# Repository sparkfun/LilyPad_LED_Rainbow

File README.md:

LilyPad LED Rainbow Board
========================

[*LilyPad LED Rainbow Board(DEV-13903)*](https://www.sparkfun.com/products/13903)

The LilyPad LED Rainbow Board is panel containing 5 strips of 7 LilyPad LED boards, one in each of 7 colors--red, green, blue, pink, purple, yellow, and white.

Features:

* 7 LED colors
* text on board to indicate color

Repository Contents
-------------------
* **/Hardware** - PCB Design files 
* **/Production** - Panel files and any pogo bed design files

Documentation
-------------
* **[SparkFun Fritzing repo](https://github.com/sparkfun/Fritzing_Parts)** - Fritzing diagrams for SparkFun products.
* **[SparkFun 3D Model repo](https://github.com/sparkfun/3D_Models)** - 3D models of SparkFun products.
* **[Hookup Guide](https://learn.sparkfun.com/tutorials/ldk-experiment-1-lighting-up-a-basic-circuit)** - Basic hookup guide for the LilyPad Rainbow LEDs.

License Information
-------------------

This product is _**open source**_!

Please review the LICENSE.md file for license information.

If you have any questions or concerns on licensing, please contact techsupport@sparkfun.com.

Distributed as-is; no warranty is given.

- Your friends at SparkFun.

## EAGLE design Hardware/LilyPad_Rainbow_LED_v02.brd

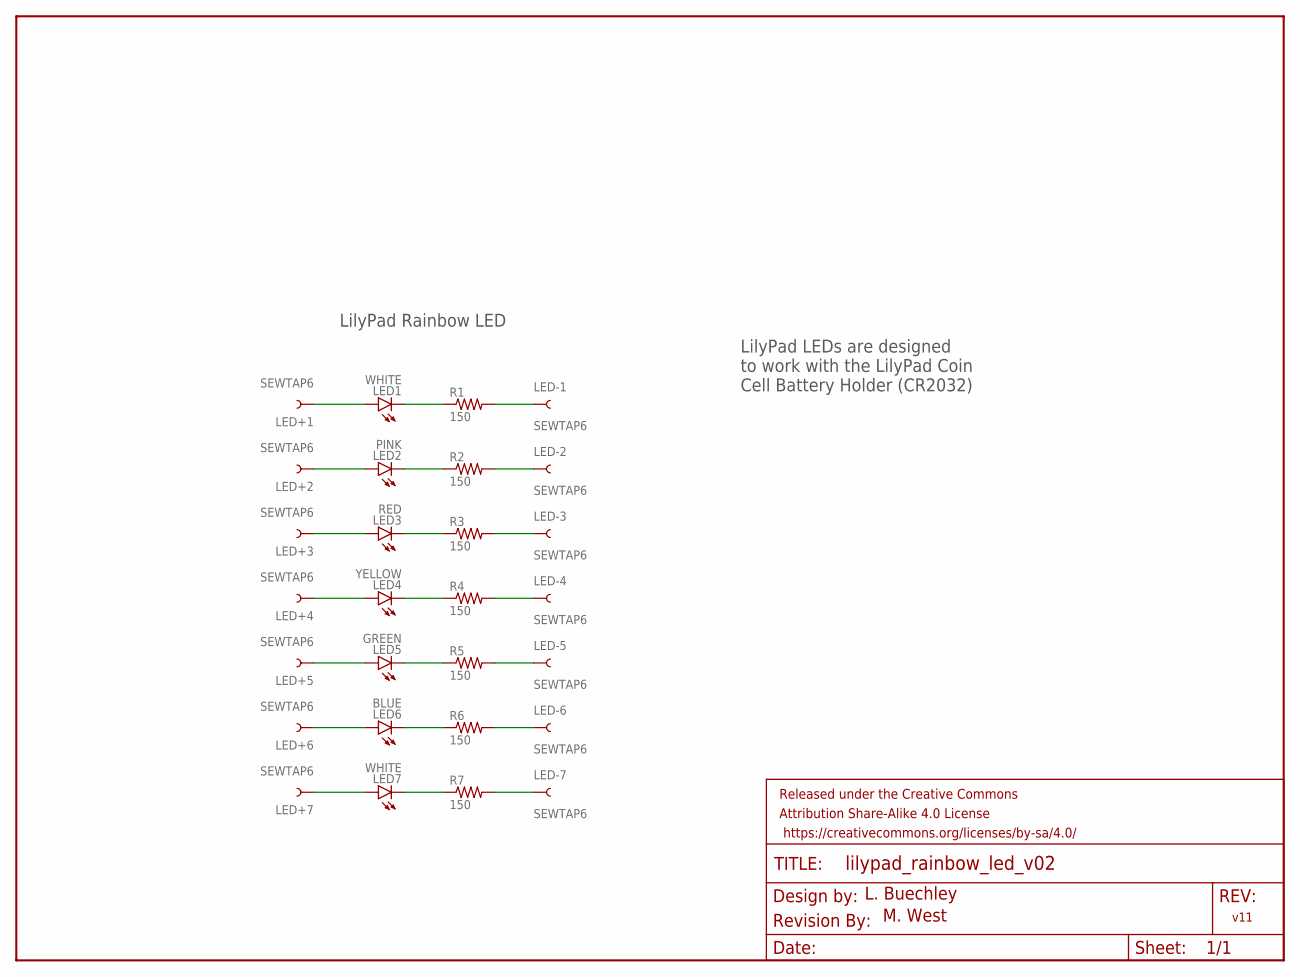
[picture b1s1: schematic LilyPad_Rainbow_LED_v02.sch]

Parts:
FRAME1: FRAME-LETTER; CREATIVE_COMMONS
LED1, LED7: WHITE; LED-1206
LED2: PINK; LED-1206
LED3: RED; LED-1206
LED4: YELLOW; LED-1206
LED5: GREEN; LED-1206
LED6: BLUE; LED-1206
LED+1, LED+2, LED+3, LED+4, LED+5, LED+6, LED+7: SEWTAP6; PETAL-SMALL-2SIDE
LED-1, LED-2, LED-3, LED-4, LED-5, LED-6, LED-7: SEWTAP6; PETAL-SMALL-2SIDE
R1, R2, R3, R4, R5, R6, R7: 150; 0603-RES
U$1: REVISION

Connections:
unnamed: LED1.A, LED+1.1
unnamed: LED1.C, R1.1
unnamed: LED-1.1, R1.2
unnamed: LED2.A, LED+2.1
unnamed: LED2.C, R2.1
unnamed: LED-2.1, R2.2
unnamed: LED3.A, LED+3.1
unnamed: LED3.C, R3.1
unnamed: LED-3.1, R3.2
unnamed: LED4.A, LED+4.1
unnamed: LED4.C, R4.1
unnamed: LED-4.1, R4.2
unnamed: LED5.A, LED+5.1
unnamed: LED5.C, R5.1
unnamed: LED-5.1, R5.2
unnamed: LED6.A, LED+6.1
unnamed: LED6.C, R6.1
unnamed: LED-6.1, R6.2
unnamed: LED7.A, LED+7.1
unnamed: LED7.C, R7.1
unnamed: LED-7.1, R7.2

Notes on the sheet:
L. Buechley
M. West
v11
LilyPad Rainbow LED
LilyPad LEDs are designed to work with the LilyPad Coin Cell Battery Holder (CR2032)

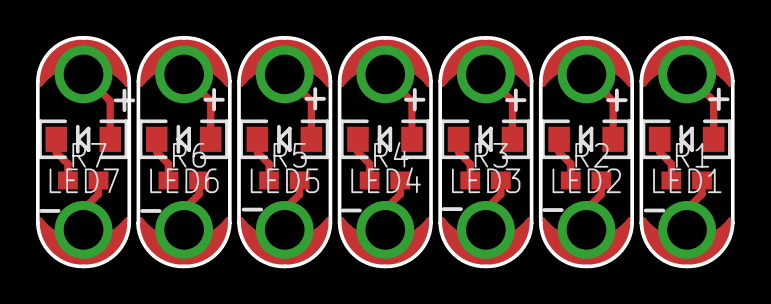
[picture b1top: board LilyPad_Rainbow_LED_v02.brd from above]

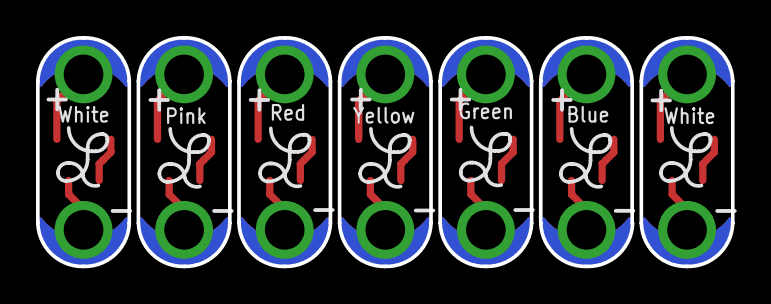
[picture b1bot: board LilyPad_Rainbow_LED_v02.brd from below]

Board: 2 copper layers, 38.6 x 12.7 mm, 37 parts (7 on the bottom side), 21 nets.

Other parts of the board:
LOGO29, LOGO30, LOGO31, LOGO32, LOGO33, LOGO34, LOGO35: LOGO-LPL; LOGO-L

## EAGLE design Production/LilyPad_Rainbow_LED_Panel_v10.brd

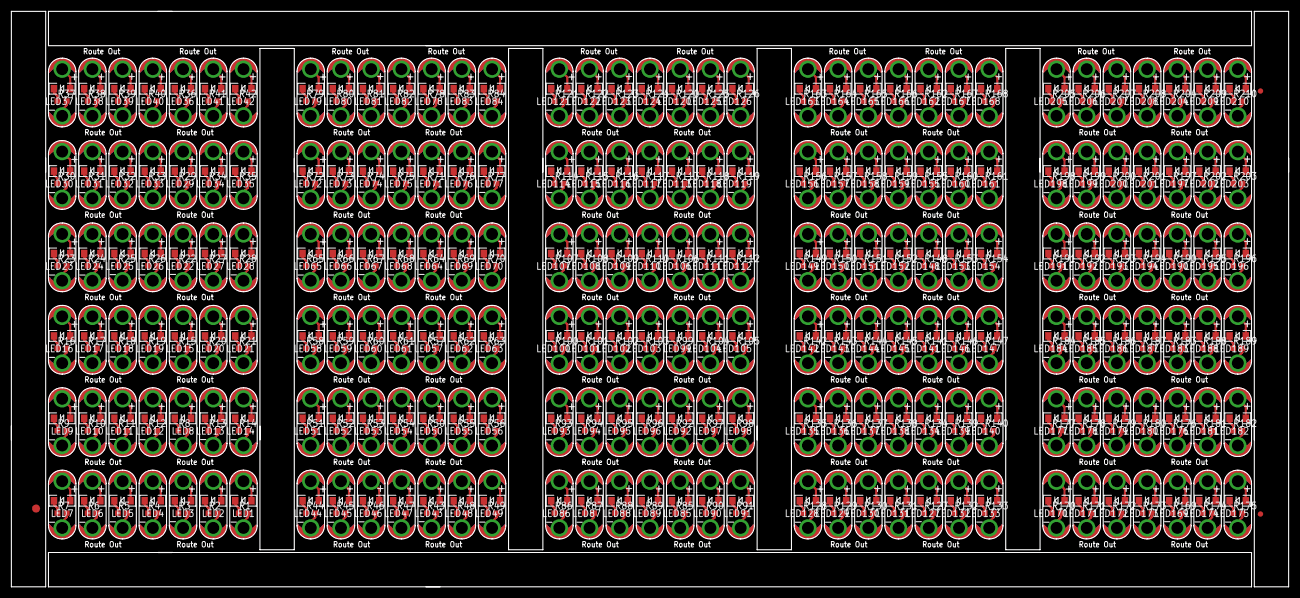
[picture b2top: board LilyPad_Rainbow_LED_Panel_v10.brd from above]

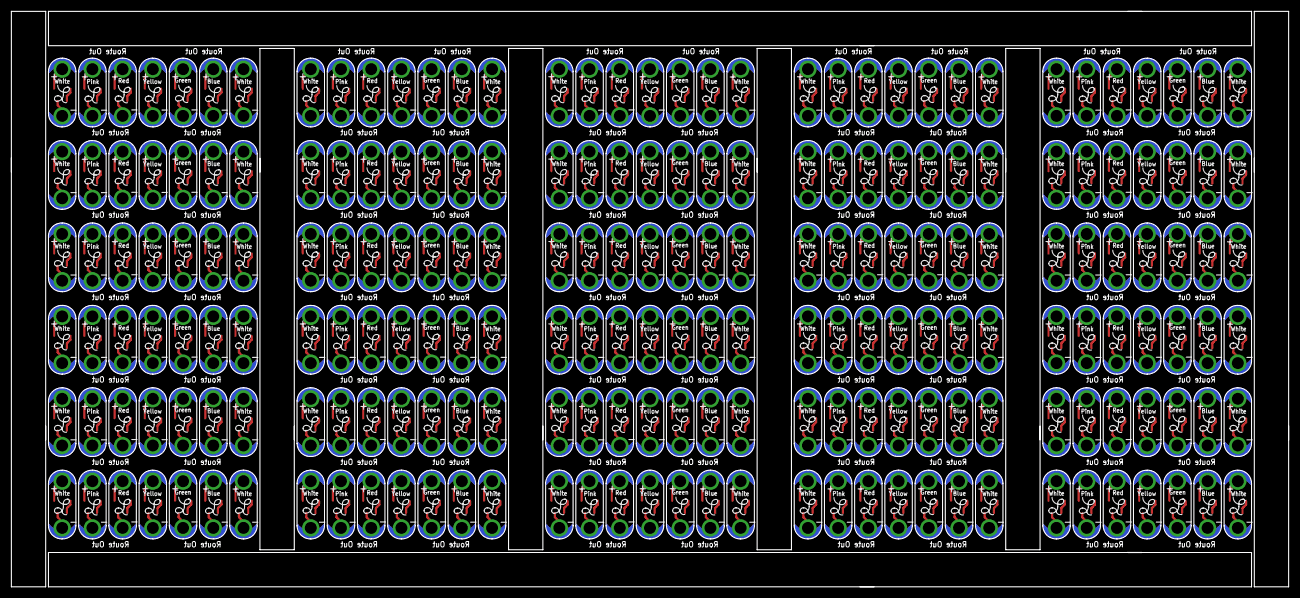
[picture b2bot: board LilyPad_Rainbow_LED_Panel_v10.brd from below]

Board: 2 copper layers, 236.2 x 106.4 mm, 1053 parts (210 on the bottom side), 630 nets.

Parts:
E$1: FIDUCIAL-1.5X3
E$13, E$14: FIDUCIAL-1X2
LED1, LED7, LED9, LED14, LED16, LED21, LED23, LED28, LED30, LED35, LED37, LED42, LED44, LED49, LED51, LED56, LED58, LED63, LED65, LED70, LED72, LED77, LED79, LED84, LED86, LED91, LED93, LED98, LED100, LED105, LED107, LED112, LED114, LED119, LED121, LED126, LED128, LED133, LED135, LED140, LED142, LED147, LED149, LED154, LED156, LED161, LED163, LED168, LED170, LED175, LED177, LED182, LED184, LED189, LED191, LED196, LED198, LED203, LED205, LED210: WHITE; LED-1206
LED2, LED13, LED20, LED27, LED34, LED41, LED48, LED55, LED62, LED69, LED76, LED83, LED90, LED97, LED104, LED111, LED118, LED125, LED132, LED139, LED146, LED153, LED160, LED167, LED174, LED181, LED188, LED195, LED202, LED209: PINK; LED-1206
LED3, LED8, LED15, LED22, LED29, LED36, LED43, LED50, LED57, LED64, LED71, LED78, LED85, LED92, LED99, LED106, LED113, LED120, LED127, LED134, LED141, LED148, LED155, LED162, LED169, LED176, LED183, LED190, LED197, LED204: RED; LED-1206
LED4, LED12, LED19, LED26, LED33, LED40, LED47, LED54, LED61, LED68, LED75, LED82, LED89, LED96, LED103, LED110, LED117, LED124, LED131, LED138, LED145, LED152, LED159, LED166, LED173, LED180, LED187, LED194, LED201, LED208: YELLOW; LED-1206
LED5, LED11, LED18, LED25, LED32, LED39, LED46, LED53, LED60, LED67, LED74, LED81, LED88, LED95, LED102, LED109, LED116, LED123, LED130, LED137, LED144, LED151, LED158, LED165, LED172, LED179, LED186, LED193, LED200, LED207: GREEN; LED-1206
LED6, LED10, LED17, LED24, LED31, LED38, LED45, LED52, LED59, LED66, LED73, LED80, LED87, LED94, LED101, LED108, LED115, LED122, LED129, LED136, LED143, LED150, LED157, LED164, LED171, LED178, LED185, LED192, LED199, LED206: BLUE; LED-1206
LED+1, LED+2, LED+3, LED+4, LED+5, LED+6, LED+7, LED+8, LED+9, LED+10, LED+11, LED+12, LED+13, LED+14, LED+15, LED+16, LED+17, LED+18, LED+19, LED+20, LED+21, LED+22, LED+23, LED+24, LED+25, LED+26, LED+27, LED+28, LED+29, LED+30, LED+31, LED+32, LED+33, LED+34, LED+35, LED+36, LED+37, LED+38, LED+39, LED+40, LED+41, LED+42, LED+43, LED+44, LED+45, LED+46, LED+47, LED+48, LED+49, LED+50, LED+51, LED+52, LED+53, LED+54, LED+55, LED+56, LED+57, LED+58, LED+59, LED+60, LED+61, LED+62, LED+63, LED+64, LED+65, LED+66, LED+67, LED+68, LED+69, LED+70, LED+71, LED+72, LED+73, LED+74, LED+75, LED+76, LED+77, LED+78, LED+79, LED+80, LED+81, LED+82, LED+83, LED+84, LED+85, LED+86, LED+87, LED+88, LED+89, LED+90, LED+91, LED+92, LED+93, LED+94, LED+95, LED+96, LED+97, LED+98, LED+99, LED+100, LED+101, LED+102, LED+103, LED+104, LED+105, LED+106, LED+107, LED+108, LED+109, LED+110, LED+111, LED+112, LED+113, LED+114, LED+115, LED+116, LED+117, LED+118, LED+119, LED+120, LED+121, LED+122, LED+123, LED+124, LED+125, LED+126, LED+127, LED+128, LED+129, LED+130, LED+131, LED+132, LED+133, LED+134, LED+135, LED+136, LED+137, LED+138, LED+139, LED+140, LED+141, LED+142, LED+143, LED+144, LED+145, LED+146, LED+147, LED+148, LED+149, LED+150, LED+151, LED+152, LED+153, LED+154, LED+155, LED+156, LED+157, LED+158, LED+159, LED+160, LED+161, LED+162, LED+163, LED+164, LED+165, LED+166, LED+167, LED+168, LED+169, LED+170, LED+171, LED+172, LED+173, LED+174, LED+175, LED+176, LED+177, LED+178, LED+179, LED+180, LED+181, LED+182, LED+183, LED+184, LED+185, LED+186, LED+187, LED+188, LED+189, LED+190, LED+191, LED+192, LED+193, LED+194, LED+195, LED+196, LED+197, LED+198, LED+199, LED+200, LED+201, LED+202, LED+203, LED+204, LED+205, LED+206, LED+207, LED+208, LED+209, LED+210: SEWTAP6; PETAL-SMALL-2SIDE
LED-1, LED-2, LED-3, LED-4, LED-5, LED-6, LED-7, LED-8, LED-9, LED-10, LED-11, LED-12, LED-13, LED-14, LED-15, LED-16, LED-17, LED-18, LED-19, LED-20, LED-21, LED-22, LED-23, LED-24, LED-25, LED-26, LED-27, LED-28, LED-29, LED-30, LED-31, LED-32, LED-33, LED-34, LED-35, LED-36, LED-37, LED-38, LED-39, LED-40, LED-41, LED-42, LED-43, LED-44, LED-45, LED-46, LED-47, LED-48, LED-49, LED-50, LED-51, LED-52, LED-53, LED-54, LED-55, LED-56, LED-57, LED-58, LED-59, LED-60, LED-61, LED-62, LED-63, LED-64, LED-65, LED-66, LED-67, LED-68, LED-69, LED-70, LED-71, LED-72, LED-73, LED-74, LED-75, LED-76, LED-77, LED-78, LED-79, LED-80, LED-81, LED-82, LED-83, LED-84, LED-85, LED-86, LED-87, LED-88, LED-89, LED-90, LED-91, LED-92, LED-93, LED-94, LED-95, LED-96, LED-97, LED-98, LED-99, LED-100, LED-101, LED-102, LED-103, LED-104, LED-105, LED-106, LED-107, LED-108, LED-109, LED-110, LED-111, LED-112, LED-113, LED-114, LED-115, LED-116, LED-117, LED-118, LED-119, LED-120, LED-121, LED-122, LED-123, LED-124, LED-125, LED-126, LED-127, LED-128, LED-129, LED-130, LED-131, LED-132, LED-133, LED-134, LED-135, LED-136, LED-137, LED-138, LED-139, LED-140, LED-141, LED-142, LED-143, LED-144, LED-145, LED-146, LED-147, LED-148, LED-149, LED-150, LED-151, LED-152, LED-153, LED-154, LED-155, LED-156, LED-157, LED-158, LED-159, LED-160, LED-161, LED-162, LED-163, LED-164, LED-165, LED-166, LED-167, LED-168, LED-169, LED-170, LED-171, LED-172, LED-173, LED-174, LED-175, LED-176, LED-177, LED-178, LED-179, LED-180, LED-181, LED-182, LED-183, LED-184, LED-185, LED-186, LED-187, LED-188, LED-189, LED-190, LED-191, LED-192, LED-193, LED-194, LED-195, LED-196, LED-197, LED-198, LED-199, LED-200, LED-201, LED-202, LED-203, LED-204, LED-205, LED-206, LED-207, LED-208, LED-209, LED-210: SEWTAP6; PETAL-SMALL-2SIDE
LOGO1, LOGO2, LOGO3, LOGO4, LOGO5, LOGO6, LOGO7, LOGO8, LOGO9, LOGO10, LOGO11, LOGO12, LOGO13, LOGO14, LOGO15, LOGO16, LOGO17, LOGO18, LOGO19, LOGO20, LOGO21, LOGO22, LOGO23, LOGO24, LOGO25, LOGO26, LOGO27, LOGO28, LOGO29, LOGO30, LOGO31, LOGO32, LOGO33, LOGO34, LOGO35, LOGO36, LOGO37, LOGO38, LOGO39, LOGO40, LOGO41, LOGO42, LOGO43, LOGO44, LOGO45, LOGO46, LOGO47, LOGO48, LOGO49, LOGO50, LOGO51, LOGO52, LOGO53, LOGO54, LOGO55, LOGO56, LOGO57, LOGO58, LOGO59, LOGO60, LOGO61, LOGO62, LOGO63, LOGO64, LOGO65, LOGO66, LOGO67, LOGO68, LOGO69, LOGO70, LOGO71, LOGO72, LOGO73, LOGO74, LOGO75, LOGO76, LOGO77, LOGO78, LOGO79, LOGO80, LOGO81, LOGO82, LOGO83, LOGO84, LOGO85, LOGO86, LOGO87, LOGO88, LOGO89, LOGO90, LOGO91, LOGO92, LOGO93, LOGO94, LOGO95, LOGO96, LOGO97, LOGO98, LOGO99, LOGO100, LOGO101, LOGO102, LOGO103, LOGO104, LOGO105, LOGO106, LOGO107, LOGO108, LOGO109, LOGO110, LOGO111, LOGO112, LOGO113, LOGO114, LOGO115, LOGO116, LOGO117, LOGO118, LOGO119, LOGO120, LOGO121, LOGO122, LOGO123, LOGO124, LOGO125, LOGO126, LOGO127, LOGO128, LOGO129, LOGO130, LOGO131, LOGO132, LOGO133, LOGO134, LOGO135, LOGO136, LOGO137, LOGO138, LOGO139, LOGO140, LOGO141, LOGO142, LOGO143, LOGO144, LOGO145, LOGO146, LOGO147, LOGO148, LOGO149, LOGO150, LOGO151, LOGO152, LOGO153, LOGO154, LOGO155, LOGO156, LOGO157, LOGO158, LOGO159, LOGO160, LOGO161, LOGO162, LOGO163, LOGO164, LOGO165, LOGO166, LOGO167, LOGO168, LOGO169, LOGO170, LOGO171, LOGO172, LOGO173, LOGO174, LOGO175, LOGO176, LOGO177, LOGO178, LOGO179, LOGO180, LOGO181, LOGO182, LOGO183, LOGO184, LOGO185, LOGO186, LOGO187, LOGO188, LOGO189, LOGO190, LOGO191, LOGO192, LOGO193, LOGO194, LOGO195, LOGO196, LOGO197, LOGO198, LOGO199, LOGO200, LOGO201, LOGO202, LOGO203, LOGO204, LOGO205, LOGO206, LOGO207, LOGO208, LOGO209, LOGO210: LOGO-LPL; LOGO-L
R1, R2, R3, R4, R5, R6, R7, R8, R9, R10, R11, R12, R13, R14, R15, R16, R17, R18, R19, R20, R21, R22, R23, R24, R25, R26, R27, R28, R29, R30, R31, R32, R33, R34, R35, R36, R37, R38, R39, R40, R41, R42, R43, R44, R45, R46, R47, R48, R49, R50, R51, R52, R53, R54, R55, R56, R57, R58, R59, R60, R61, R62, R63, R64, R65, R66, R67, R68, R69, R70, R71, R72, R73, R74, R75, R76, R77, R78, R79, R80, R81, R82, R83, R84, R85, R86, R87, R88, R89, R90, R91, R92, R93, R94, R95, R96, R97, R98, R99, R100, R101, R102, R103, R104, R105, R106, R107, R108, R109, R110, R111, R112, R113, R114, R115, R116, R117, R118, R119, R120, R121, R122, R123, R124, R125, R126, R127, R128, R129, R130, R131, R132, R133, R134, R135, R136, R137, R138, R139, R140, R141, R142, R143, R144, R145, R146, R147, R148, R149, R150, R151, R152, R153, R154, R155, R156, R157, R158, R159, R160, R161, R162, R163, R164, R165, R166, R167, R168, R169, R170, R171, R172, R173, R174, R175, R176, R177, R178, R179, R180, R181, R182, R183, R184, R185, R186, R187, R188, R189, R190, R191, R192, R193, R194, R195, R196, R197, R198, R199, R200, R201, R202, R203, R204, R205, R206, R207, R208, R209, R210: 150; 0603-RES

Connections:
unnamed: LED1.A, LED+1.1
unnamed: LED1.C, R1.1
unnamed: LED-1.1, R1.2
unnamed: LED2.A, LED+2.1
unnamed: LED2.C, R2.1
unnamed: LED-2.1, R2.2
unnamed: LED3.A, LED+3.1
unnamed: LED3.C, R3.1
unnamed: LED-3.1, R3.2
unnamed: LED4.A, LED+4.1
unnamed: LED4.C, R4.1
unnamed: LED-4.1, R4.2
unnamed: LED5.A, LED+5.1
unnamed: LED5.C, R5.1
unnamed: LED-5.1, R5.2
unnamed: LED6.A, LED+6.1
unnamed: LED6.C, R6.1
unnamed: LED-6.1, R6.2
unnamed: LED7.A, LED+7.1
unnamed: LED7.C, R7.1
unnamed: LED-7.1, R7.2
unnamed: LED8.C, R8.1
unnamed: LED8.A, LED+8.1
unnamed: LED-8.1, R8.2
unnamed: LED9.C, R9.1
unnamed: LED9.A, LED+9.1
unnamed: LED-9.1, R9.2
unnamed: LED10.C, R10.1
unnamed: LED10.A, LED+10.1
unnamed: LED-10.1, R10.2
unnamed: LED11.C, R11.1
unnamed: LED11.A, LED+11.1
unnamed: LED-11.1, R11.2
unnamed: LED12.C, R12.1
unnamed: LED12.A, LED+12.1
unnamed: LED-12.1, R12.2
unnamed: LED13.C, R13.1
unnamed: LED13.A, LED+13.1
unnamed: LED-13.1, R13.2
unnamed: LED14.C, R14.1
unnamed: LED14.A, LED+14.1
unnamed: LED-14.1, R14.2
unnamed: LED15.C, R15.1
unnamed: LED15.A, LED+15.1
unnamed: LED-15.1, R15.2
unnamed: LED16.C, R16.1
unnamed: LED16.A, LED+16.1
unnamed: LED-16.1, R16.2
unnamed: LED17.C, R17.1
unnamed: LED17.A, LED+17.1
unnamed: LED-17.1, R17.2
unnamed: LED18.C, R18.1
unnamed: LED18.A, LED+18.1
unnamed: LED-18.1, R18.2
unnamed: LED19.C, R19.1
unnamed: LED19.A, LED+19.1
unnamed: LED-19.1, R19.2
unnamed: LED20.C, R20.1
unnamed: LED20.A, LED+20.1
unnamed: LED-20.1, R20.2
unnamed: LED21.C, R21.1
unnamed: LED21.A, LED+21.1
unnamed: LED-21.1, R21.2
unnamed: LED22.C, R22.1
unnamed: LED22.A, LED+22.1
unnamed: LED-22.1, R22.2
unnamed: LED23.C, R23.1
unnamed: LED23.A, LED+23.1
unnamed: LED-23.1, R23.2
unnamed: LED24.C, R24.1
unnamed: LED24.A, LED+24.1
unnamed: LED-24.1, R24.2
unnamed: LED25.C, R25.1
unnamed: LED25.A, LED+25.1
unnamed: LED-25.1, R25.2
unnamed: LED26.C, R26.1
unnamed: LED26.A, LED+26.1
unnamed: LED-26.1, R26.2
unnamed: LED27.C, R27.1
unnamed: LED27.A, LED+27.1
unnamed: LED-27.1, R27.2
unnamed: LED28.C, R28.1
unnamed: LED28.A, LED+28.1
unnamed: LED-28.1, R28.2
unnamed: LED29.C, R29.1
unnamed: LED29.A, LED+29.1
unnamed: LED-29.1, R29.2
unnamed: LED30.C, R30.1
unnamed: LED30.A, LED+30.1
unnamed: LED-30.1, R30.2
unnamed: LED31.C, R31.1
unnamed: LED31.A, LED+31.1
unnamed: LED-31.1, R31.2
unnamed: LED32.C, R32.1
unnamed: LED32.A, LED+32.1
unnamed: LED-32.1, R32.2
unnamed: LED33.C, R33.1
unnamed: LED33.A, LED+33.1
unnamed: LED-33.1, R33.2
unnamed: LED34.C, R34.1
unnamed: LED34.A, LED+34.1
unnamed: LED-34.1, R34.2
unnamed: LED35.C, R35.1
unnamed: LED35.A, LED+35.1
unnamed: LED-35.1, R35.2
unnamed: LED36.C, R36.1
unnamed: LED36.A, LED+36.1
unnamed: LED-36.1, R36.2
unnamed: LED37.C, R37.1
unnamed: LED37.A, LED+37.1
unnamed: LED-37.1, R37.2
unnamed: LED38.C, R38.1
unnamed: LED38.A, LED+38.1
unnamed: LED-38.1, R38.2
unnamed: LED39.C, R39.1
unnamed: LED39.A, LED+39.1
unnamed: LED-39.1, R39.2
unnamed: LED40.C, R40.1
unnamed: LED40.A, LED+40.1
unnamed: LED-40.1, R40.2
unnamed: LED41.C, R41.1
unnamed: LED41.A, LED+41.1
unnamed: LED-41.1, R41.2
unnamed: LED42.C, R42.1
unnamed: LED42.A, LED+42.1
unnamed: LED-42.1, R42.2
unnamed: LED43.C, R43.1
unnamed: LED43.A, LED+43.1
unnamed: LED-43.1, R43.2
unnamed: LED44.C, R44.1
unnamed: LED44.A, LED+44.1
unnamed: LED-44.1, R44.2
unnamed: LED45.C, R45.1
unnamed: LED45.A, LED+45.1
unnamed: LED-45.1, R45.2
unnamed: LED46.C, R46.1
unnamed: LED46.A, LED+46.1
unnamed: LED-46.1, R46.2
unnamed: LED47.C, R47.1
unnamed: LED47.A, LED+47.1
unnamed: LED-47.1, R47.2
unnamed: LED48.C, R48.1
unnamed: LED48.A, LED+48.1
unnamed: LED-48.1, R48.2
unnamed: LED49.C, R49.1
unnamed: LED49.A, LED+49.1
unnamed: LED-49.1, R49.2
unnamed: LED50.C, R50.1
unnamed: LED50.A, LED+50.1
unnamed: LED-50.1, R50.2
unnamed: LED51.C, R51.1
unnamed: LED51.A, LED+51.1
unnamed: LED-51.1, R51.2
unnamed: LED52.C, R52.1
unnamed: LED52.A, LED+52.1
unnamed: LED-52.1, R52.2
unnamed: LED53.C, R53.1
unnamed: LED53.A, LED+53.1
unnamed: LED-53.1, R53.2
unnamed: LED54.C, R54.1
unnamed: LED54.A, LED+54.1
unnamed: LED-54.1, R54.2
unnamed: LED55.C, R55.1
unnamed: LED55.A, LED+55.1
unnamed: LED-55.1, R55.2
unnamed: LED56.C, R56.1
unnamed: LED56.A, LED+56.1
unnamed: LED-56.1, R56.2
unnamed: LED57.C, R57.1
unnamed: LED57.A, LED+57.1
unnamed: LED-57.1, R57.2
unnamed: LED58.C, R58.1
unnamed: LED58.A, LED+58.1
unnamed: LED-58.1, R58.2
unnamed: LED59.C, R59.1
unnamed: LED59.A, LED+59.1
unnamed: LED-59.1, R59.2
unnamed: LED60.C, R60.1
unnamed: LED60.A, LED+60.1
unnamed: LED-60.1, R60.2
unnamed: LED61.C, R61.1
unnamed: LED61.A, LED+61.1
unnamed: LED-61.1, R61.2
unnamed: LED62.C, R62.1
unnamed: LED62.A, LED+62.1
unnamed: LED-62.1, R62.2
unnamed: LED63.C, R63.1
unnamed: LED63.A, LED+63.1
unnamed: LED-63.1, R63.2
unnamed: LED64.C, R64.1
unnamed: LED64.A, LED+64.1
unnamed: LED-64.1, R64.2
unnamed: LED65.C, R65.1
unnamed: LED65.A, LED+65.1
unnamed: LED-65.1, R65.2
unnamed: LED66.C, R66.1
unnamed: LED66.A, LED+66.1
unnamed: LED-66.1, R66.2
unnamed: LED67.C, R67.1
unnamed: LED67.A, LED+67.1
unnamed: LED-67.1, R67.2
unnamed: LED68.C, R68.1
unnamed: LED68.A, LED+68.1
unnamed: LED-68.1, R68.2
unnamed: LED69.C, R69.1
unnamed: LED69.A, LED+69.1
unnamed: LED-69.1, R69.2
unnamed: LED70.C, R70.1
unnamed: LED70.A, LED+70.1
unnamed: LED-70.1, R70.2
unnamed: LED71.C, R71.1
unnamed: LED71.A, LED+71.1
unnamed: LED-71.1, R71.2
unnamed: LED72.C, R72.1
unnamed: LED72.A, LED+72.1
unnamed: LED-72.1, R72.2
unnamed: LED73.C, R73.1
unnamed: LED73.A, LED+73.1
unnamed: LED-73.1, R73.2
unnamed: LED74.C, R74.1
unnamed: LED74.A, LED+74.1
unnamed: LED-74.1, R74.2
unnamed: LED75.C, R75.1
unnamed: LED75.A, LED+75.1
unnamed: LED-75.1, R75.2
unnamed: LED76.C, R76.1
unnamed: LED76.A, LED+76.1
unnamed: LED-76.1, R76.2
unnamed: LED77.C, R77.1
unnamed: LED77.A, LED+77.1
unnamed: LED-77.1, R77.2
unnamed: LED78.C, R78.1
unnamed: LED78.A, LED+78.1
unnamed: LED-78.1, R78.2
unnamed: LED79.C, R79.1
unnamed: LED79.A, LED+79.1
unnamed: LED-79.1, R79.2
unnamed: LED80.C, R80.1
unnamed: LED80.A, LED+80.1
unnamed: LED-80.1, R80.2
unnamed: LED81.C, R81.1
unnamed: LED81.A, LED+81.1
unnamed: LED-81.1, R81.2
unnamed: LED82.C, R82.1
unnamed: LED82.A, LED+82.1
unnamed: LED-82.1, R82.2
unnamed: LED83.C, R83.1
unnamed: LED83.A, LED+83.1
unnamed: LED-83.1, R83.2
unnamed: LED84.C, R84.1
unnamed: LED84.A, LED+84.1
unnamed: LED-84.1, R84.2
unnamed: LED85.C, R85.1
unnamed: LED85.A, LED+85.1
unnamed: LED-85.1, R85.2
unnamed: LED86.C, R86.1
unnamed: LED86.A, LED+86.1
unnamed: LED-86.1, R86.2
unnamed: LED87.C, R87.1
unnamed: LED87.A, LED+87.1
unnamed: LED-87.1, R87.2
unnamed: LED88.C, R88.1
unnamed: LED88.A, LED+88.1
unnamed: LED-88.1, R88.2
unnamed: LED89.C, R89.1
unnamed: LED89.A, LED+89.1
unnamed: LED-89.1, R89.2
unnamed: LED90.C, R90.1
unnamed: LED90.A, LED+90.1
unnamed: LED-90.1, R90.2
unnamed: LED91.C, R91.1
unnamed: LED91.A, LED+91.1
unnamed: LED-91.1, R91.2
unnamed: LED92.C, R92.1
unnamed: LED92.A, LED+92.1
unnamed: LED-92.1, R92.2
unnamed: LED93.C, R93.1
unnamed: LED93.A, LED+93.1
unnamed: LED-93.1, R93.2
unnamed: LED94.C, R94.1
unnamed: LED94.A, LED+94.1
unnamed: LED-94.1, R94.2
unnamed: LED95.C, R95.1
unnamed: LED95.A, LED+95.1
unnamed: LED-95.1, R95.2
unnamed: LED96.C, R96.1
unnamed: LED96.A, LED+96.1
unnamed: LED-96.1, R96.2
unnamed: LED97.C, R97.1
unnamed: LED97.A, LED+97.1
unnamed: LED-97.1, R97.2
unnamed: LED98.C, R98.1
unnamed: LED98.A, LED+98.1
unnamed: LED-98.1, R98.2
unnamed: LED99.C, R99.1
unnamed: LED99.A, LED+99.1
unnamed: LED-99.1, R99.2
unnamed: LED100.C, R100.1
unnamed: LED100.A, LED+100.1
unnamed: LED-100.1, R100.2
unnamed: LED101.C, R101.1
unnamed: LED101.A, LED+101.1
unnamed: LED-101.1, R101.2
unnamed: LED102.C, R102.1
unnamed: LED102.A, LED+102.1
unnamed: LED-102.1, R102.2
unnamed: LED103.C, R103.1
unnamed: LED103.A, LED+103.1
unnamed: LED-103.1, R103.2
unnamed: LED104.C, R104.1
unnamed: LED104.A, LED+104.1
unnamed: LED-104.1, R104.2
unnamed: LED105.C, R105.1
unnamed: LED105.A, LED+105.1
unnamed: LED-105.1, R105.2
unnamed: LED106.C, R106.1
unnamed: LED106.A, LED+106.1
unnamed: LED-106.1, R106.2
unnamed: LED107.C, R107.1
unnamed: LED107.A, LED+107.1
unnamed: LED-107.1, R107.2
unnamed: LED108.C, R108.1
unnamed: LED108.A, LED+108.1
unnamed: LED-108.1, R108.2
unnamed: LED109.C, R109.1
unnamed: LED109.A, LED+109.1
unnamed: LED-109.1, R109.2
unnamed: LED110.C, R110.1
unnamed: LED110.A, LED+110.1
unnamed: LED-110.1, R110.2
unnamed: LED111.C, R111.1
unnamed: LED111.A, LED+111.1
unnamed: LED-111.1, R111.2
unnamed: LED112.C, R112.1
unnamed: LED112.A, LED+112.1
unnamed: LED-112.1, R112.2
unnamed: LED113.C, R113.1
unnamed: LED113.A, LED+113.1
unnamed: LED-113.1, R113.2
unnamed: LED114.C, R114.1
unnamed: LED114.A, LED+114.1
unnamed: LED-114.1, R114.2
unnamed: LED115.C, R115.1
unnamed: LED115.A, LED+115.1
unnamed: LED-115.1, R115.2
unnamed: LED116.C, R116.1
unnamed: LED116.A, LED+116.1
unnamed: LED-116.1, R116.2
unnamed: LED117.C, R117.1
unnamed: LED117.A, LED+117.1
unnamed: LED-117.1, R117.2
unnamed: LED118.C, R118.1
unnamed: LED118.A, LED+118.1
unnamed: LED-118.1, R118.2
unnamed: LED119.C, R119.1
unnamed: LED119.A, LED+119.1
unnamed: LED-119.1, R119.2
unnamed: LED120.C, R120.1
unnamed: LED120.A, LED+120.1
unnamed: LED-120.1, R120.2
unnamed: LED121.C, R121.1
unnamed: LED121.A, LED+121.1
unnamed: LED-121.1, R121.2
unnamed: LED122.C, R122.1
unnamed: LED122.A, LED+122.1
unnamed: LED-122.1, R122.2
unnamed: LED123.C, R123.1
unnamed: LED123.A, LED+123.1
unnamed: LED-123.1, R123.2
unnamed: LED124.C, R124.1
unnamed: LED124.A, LED+124.1
unnamed: LED-124.1, R124.2
unnamed: LED125.C, R125.1
unnamed: LED125.A, LED+125.1
unnamed: LED-125.1, R125.2
unnamed: LED126.C, R126.1
unnamed: LED126.A, LED+126.1
unnamed: LED-126.1, R126.2
unnamed: LED127.C, R127.1
unnamed: LED127.A, LED+127.1
unnamed: LED-127.1, R127.2
unnamed: LED128.C, R128.1
unnamed: LED128.A, LED+128.1
unnamed: LED-128.1, R128.2
unnamed: LED129.C, R129.1
unnamed: LED129.A, LED+129.1
unnamed: LED-129.1, R129.2
unnamed: LED130.C, R130.1
unnamed: LED130.A, LED+130.1
unnamed: LED-130.1, R130.2
unnamed: LED131.C, R131.1
unnamed: LED131.A, LED+131.1
unnamed: LED-131.1, R131.2
unnamed: LED132.C, R132.1
unnamed: LED132.A, LED+132.1
unnamed: LED-132.1, R132.2
unnamed: LED133.C, R133.1
unnamed: LED133.A, LED+133.1
unnamed: LED-133.1, R133.2
unnamed: LED134.C, R134.1
unnamed: LED134.A, LED+134.1
unnamed: LED-134.1, R134.2
unnamed: LED135.C, R135.1
unnamed: LED135.A, LED+135.1
unnamed: LED-135.1, R135.2
unnamed: LED136.C, R136.1
unnamed: LED136.A, LED+136.1
unnamed: LED-136.1, R136.2
unnamed: LED137.C, R137.1
unnamed: LED137.A, LED+137.1
unnamed: LED-137.1, R137.2
unnamed: LED138.C, R138.1
unnamed: LED138.A, LED+138.1
unnamed: LED-138.1, R138.2
unnamed: LED139.C, R139.1
unnamed: LED139.A, LED+139.1
unnamed: LED-139.1, R139.2
unnamed: LED140.C, R140.1
unnamed: LED140.A, LED+140.1
unnamed: LED-140.1, R140.2
unnamed: LED141.C, R141.1
unnamed: LED141.A, LED+141.1
unnamed: LED-141.1, R141.2
unnamed: LED142.C, R142.1
unnamed: LED142.A, LED+142.1
unnamed: LED-142.1, R142.2
unnamed: LED143.C, R143.1
unnamed: LED143.A, LED+143.1
unnamed: LED-143.1, R143.2
unnamed: LED144.C, R144.1
unnamed: LED144.A, LED+144.1
unnamed: LED-144.1, R144.2
unnamed: LED145.C, R145.1
unnamed: LED145.A, LED+145.1
unnamed: LED-145.1, R145.2
unnamed: LED146.C, R146.1
unnamed: LED146.A, LED+146.1
unnamed: LED-146.1, R146.2
unnamed: LED147.C, R147.1
unnamed: LED147.A, LED+147.1
unnamed: LED-147.1, R147.2
unnamed: LED148.C, R148.1
unnamed: LED148.A, LED+148.1
unnamed: LED-148.1, R148.2
unnamed: LED149.C, R149.1
unnamed: LED149.A, LED+149.1
unnamed: LED-149.1, R149.2
unnamed: LED150.C, R150.1
unnamed: LED150.A, LED+150.1
unnamed: LED-150.1, R150.2
unnamed: LED151.C, R151.1
unnamed: LED151.A, LED+151.1
unnamed: LED-151.1, R151.2
unnamed: LED152.C, R152.1
unnamed: LED152.A, LED+152.1
unnamed: LED-152.1, R152.2
unnamed: LED153.C, R153.1
unnamed: LED153.A, LED+153.1
unnamed: LED-153.1, R153.2
unnamed: LED154.C, R154.1
unnamed: LED154.A, LED+154.1
unnamed: LED-154.1, R154.2
unnamed: LED155.C, R155.1
unnamed: LED155.A, LED+155.1
unnamed: LED-155.1, R155.2
unnamed: LED156.C, R156.1
unnamed: LED156.A, LED+156.1
unnamed: LED-156.1, R156.2
unnamed: LED157.C, R157.1
unnamed: LED157.A, LED+157.1
unnamed: LED-157.1, R157.2
unnamed: LED158.C, R158.1
unnamed: LED158.A, LED+158.1
unnamed: LED-158.1, R158.2
unnamed: LED159.C, R159.1
unnamed: LED159.A, LED+159.1
unnamed: LED-159.1, R159.2
unnamed: LED160.C, R160.1
unnamed: LED160.A, LED+160.1
unnamed: LED-160.1, R160.2
unnamed: LED161.C, R161.1
unnamed: LED161.A, LED+161.1
unnamed: LED-161.1, R161.2
unnamed: LED162.C, R162.1
unnamed: LED162.A, LED+162.1
unnamed: LED-162.1, R162.2
unnamed: LED163.C, R163.1
unnamed: LED163.A, LED+163.1
unnamed: LED-163.1, R163.2
unnamed: LED164.C, R164.1
unnamed: LED164.A, LED+164.1
unnamed: LED-164.1, R164.2
unnamed: LED165.C, R165.1
unnamed: LED165.A, LED+165.1
unnamed: LED-165.1, R165.2
unnamed: LED166.C, R166.1
unnamed: LED166.A, LED+166.1
unnamed: LED-166.1, R166.2
unnamed: LED167.C, R167.1
unnamed: LED167.A, LED+167.1
unnamed: LED-167.1, R167.2
unnamed: LED168.C, R168.1
unnamed: LED168.A, LED+168.1
unnamed: LED-168.1, R168.2
unnamed: LED169.C, R169.1
unnamed: LED169.A, LED+169.1
unnamed: LED-169.1, R169.2
unnamed: LED170.C, R170.1
unnamed: LED170.A, LED+170.1
unnamed: LED-170.1, R170.2
unnamed: LED171.C, R171.1
unnamed: LED171.A, LED+171.1
unnamed: LED-171.1, R171.2
unnamed: LED172.C, R172.1
unnamed: LED172.A, LED+172.1
unnamed: LED-172.1, R172.2
unnamed: LED173.C, R173.1
unnamed: LED173.A, LED+173.1
unnamed: LED-173.1, R173.2
unnamed: LED174.C, R174.1
unnamed: LED174.A, LED+174.1
unnamed: LED-174.1, R174.2
unnamed: LED175.C, R175.1
unnamed: LED175.A, LED+175.1
unnamed: LED-175.1, R175.2
unnamed: LED176.C, R176.1
unnamed: LED176.A, LED+176.1
unnamed: LED-176.1, R176.2
unnamed: LED177.C, R177.1
unnamed: LED177.A, LED+177.1
unnamed: LED-177.1, R177.2
unnamed: LED178.C, R178.1
unnamed: LED178.A, LED+178.1
unnamed: LED-178.1, R178.2
unnamed: LED179.C, R179.1
unnamed: LED179.A, LED+179.1
unnamed: LED-179.1, R179.2
unnamed: LED180.C, R180.1
unnamed: LED180.A, LED+180.1
unnamed: LED-180.1, R180.2
unnamed: LED181.C, R181.1
unnamed: LED181.A, LED+181.1
unnamed: LED-181.1, R181.2
unnamed: LED182.C, R182.1
unnamed: LED182.A, LED+182.1
unnamed: LED-182.1, R182.2
unnamed: LED183.C, R183.1
unnamed: LED183.A, LED+183.1
unnamed: LED-183.1, R183.2
unnamed: LED184.C, R184.1
unnamed: LED184.A, LED+184.1
unnamed: LED-184.1, R184.2
unnamed: LED185.C, R185.1
unnamed: LED185.A, LED+185.1
unnamed: LED-185.1, R185.2
unnamed: LED186.C, R186.1
unnamed: LED186.A, LED+186.1
unnamed: LED-186.1, R186.2
unnamed: LED187.C, R187.1
unnamed: LED187.A, LED+187.1
unnamed: LED-187.1, R187.2
unnamed: LED188.C, R188.1
unnamed: LED188.A, LED+188.1
unnamed: LED-188.1, R188.2
unnamed: LED189.C, R189.1
unnamed: LED189.A, LED+189.1
unnamed: LED-189.1, R189.2
unnamed: LED190.C, R190.1
unnamed: LED190.A, LED+190.1
unnamed: LED-190.1, R190.2
unnamed: LED191.C, R191.1
unnamed: LED191.A, LED+191.1
unnamed: LED-191.1, R191.2
unnamed: LED192.C, R192.1
unnamed: LED192.A, LED+192.1
unnamed: LED-192.1, R192.2
unnamed: LED193.C, R193.1
unnamed: LED193.A, LED+193.1
unnamed: LED-193.1, R193.2
unnamed: LED194.C, R194.1
unnamed: LED194.A, LED+194.1
unnamed: LED-194.1, R194.2
unnamed: LED195.C, R195.1
unnamed: LED195.A, LED+195.1
unnamed: LED-195.1, R195.2
unnamed: LED196.C, R196.1
unnamed: LED196.A, LED+196.1
unnamed: LED-196.1, R196.2
unnamed: LED197.C, R197.1
unnamed: LED197.A, LED+197.1
unnamed: LED-197.1, R197.2
unnamed: LED198.C, R198.1
unnamed: LED198.A, LED+198.1
unnamed: LED-198.1, R198.2
unnamed: LED199.C, R199.1
unnamed: LED199.A, LED+199.1
unnamed: LED-199.1, R199.2
unnamed: LED200.C, R200.1
unnamed: LED200.A, LED+200.1
unnamed: LED-200.1, R200.2
unnamed: LED201.C, R201.1
unnamed: LED201.A, LED+201.1
unnamed: LED-201.1, R201.2
unnamed: LED202.C, R202.1
unnamed: LED202.A, LED+202.1
unnamed: LED-202.1, R202.2
unnamed: LED203.C, R203.1
unnamed: LED203.A, LED+203.1
unnamed: LED-203.1, R203.2
unnamed: LED204.C, R204.1
unnamed: LED204.A, LED+204.1
unnamed: LED-204.1, R204.2
unnamed: LED205.C, R205.1
unnamed: LED205.A, LED+205.1
unnamed: LED-205.1, R205.2
unnamed: LED206.C, R206.1
unnamed: LED206.A, LED+206.1
unnamed: LED-206.1, R206.2
unnamed: LED207.C, R207.1
unnamed: LED207.A, LED+207.1
unnamed: LED-207.1, R207.2
unnamed: LED208.C, R208.1
unnamed: LED208.A, LED+208.1
unnamed: LED-208.1, R208.2
unnamed: LED209.C, R209.1
unnamed: LED209.A, LED+209.1
unnamed: LED-209.1, R209.2
unnamed: LED210.C, R210.1
unnamed: LED210.A, LED+210.1
unnamed: LED-210.1, R210.2

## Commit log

2013-04-30 Initial Commit
    Eagle files and Readme
2013-06-06 v10 Production ready
    added fiducials & doubled panel size.
    added SFE flame logos to indicate where to cut the panel in half
2013-08-30 Update README.md
    Adding link to product page
2016-04-18 updating board and Schematic files
2016-04-19 Updated Board and Schemtic Files
2016-04-19 updated Board and Schematic files
2016-04-19 updated fies
2016-04-22 Updated Board File - Corrected SewTap
2016-04-22 Board and Schematic files are Consistent
2016-04-25 updated Brd and Sch files (in Sync)
2016-04-25 updated version number and approved DRC errors
2016-06-09 Updated brd file
2016-06-16 Updated Board File and Sch File per Eng. Design Review
2016-06-16 Updated Brd File per QC
2016-06-21 created panel v10
2016-10-14 Updating README with product links, updating README
2016-10-14 Updating product links

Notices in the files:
parts and their libraries:
SparkFun-LED: Licensing: Creative Commons ShareAlike 4.0 International - https://creativecommons.org/licenses/by-sa/4.0
SparkFun-Aesthetics: Released under the Creative Commons Attribution Share-Alike 4.0 License
SparkFun-Aesthetics: https://creativecommons.org/licenses/by-sa/4.0
